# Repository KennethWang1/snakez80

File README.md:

# snakez80

Snake running on a custom Z80 computer. Made for TEJ4MP.

# Requirements

- A Z8400-compatible CPU.
- A TMM2016BP memory chip or compatible.
- A PCB with the KiCAD design (TODO: add link to kicad design), or a breadboard with the equivalent schematic.
- An Arduino Nano.

Connect everything, flash the [loader code](./loader) with the Arduino IDE, and open [`web/index.html`](web/index.html) or https://creative0708.github.io/snakez80/ in a browser.

Have fun.

# Building `rom.hpp` from source

You'll need a set of [z88dk](https://github.com/z88dk/z88dk) binaries **with** SDCC. Follow its [installation instructions](https://github.com/z88dk/z88dk/wiki/installation) to install it.

Run `make` to build the ROM and convert the ROM into Arduino code.

# License

If for some reason you want to use this code, it's licensed under the [MIT License](/LICENSE).

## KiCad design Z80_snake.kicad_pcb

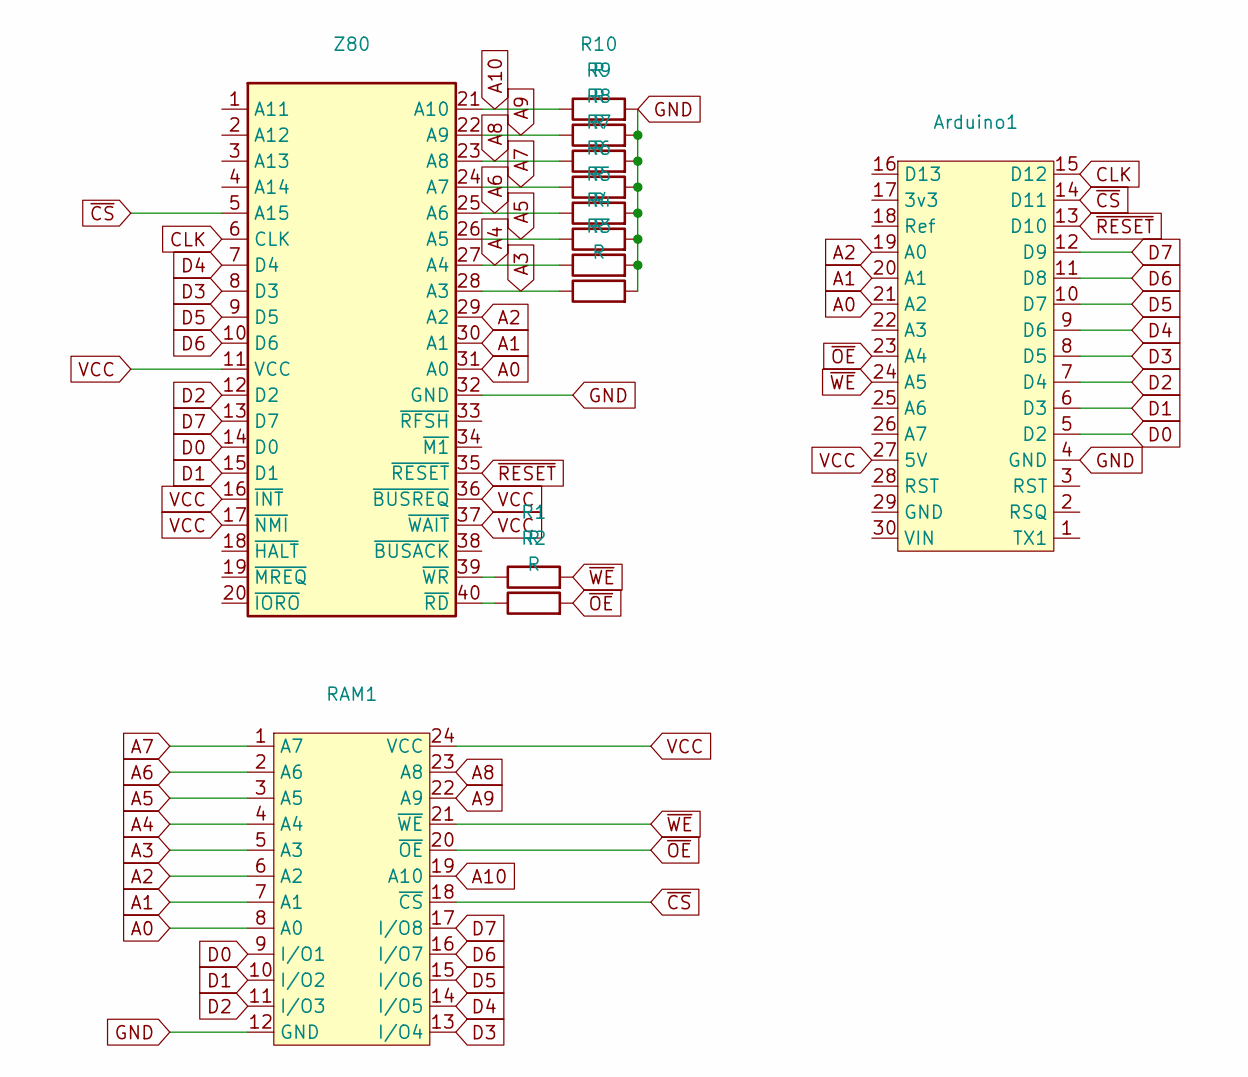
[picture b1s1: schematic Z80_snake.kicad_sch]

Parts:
Arduino1: Arduino_Nano
R1, R2, R3, R4, R5, R6, R7, R8, R9, R10: R; R_Axial_DIN0204_L3.6mm_D1.6mm_P7.62mm_Horizontal
RAM1: RAM
Z80: Z8400AB1

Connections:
A0: Arduino1.21 (A2), RAM1.8 (A0), Z80.31 (A0)
A1: Arduino1.20 (A1), RAM1.7 (A1), Z80.30 (A1)
A2: Arduino1.19 (A0), RAM1.6 (A2), Z80.29 (A2)
A3: R3.1, RAM1.5 (A3), Z80.28 (A3)
A4: R4.1, RAM1.4 (A4), Z80.27 (A4)
A5: R5.1, RAM1.3 (A5), Z80.26 (A5)
A6: R6.1, RAM1.2 (A6), Z80.25 (A6)
A7: R7.1, RAM1.1 (A7), Z80.24 (A7)
A8: R8.1, RAM1.23 (A8), Z80.23 (A8)
A9: R9.1, RAM1.22 (A9), Z80.22 (A9)
A10: R10.1, RAM1.19 (A10), Z80.21 (A10)
CLK: Arduino1.15 (D12), Z80.6 (CLK)
D0: Arduino1.5 (D2), RAM1.9 (I/O1), Z80.14 (D0)
D1: Arduino1.6 (D3), RAM1.10 (I/O2), Z80.15 (D1)
D2: Arduino1.7 (D4), RAM1.11 (I/O3), Z80.12 (D2)
D3: Arduino1.8 (D5), RAM1.13 (I/O4), Z80.8 (D3)
D4: Arduino1.9 (D6), RAM1.14 (I/O5), Z80.7 (D4)
D5: Arduino1.10 (D7), RAM1.15 (I/O6), Z80.9 (D5)
D6: Arduino1.11 (D8), RAM1.16 (I/O7), Z80.10 (D6)
D7: Arduino1.12 (D9), RAM1.17 (I/O8), Z80.13 (D7)
GND: Arduino1.4 (GND), R3.2, R4.2, R5.2, R6.2, R7.2, R8.2, R9.2, R10.2, RAM1.12 (GND), Z80.32 (GND)
unnamed: R2.1, Z80.40 (~RD)
unnamed: R1.1, Z80.39 (~WR)
VCC: Arduino1.27 (5V), RAM1.24 (VCC), Z80.11 (VCC), Z80.16 (~INT), Z80.17 (~NMI), Z80.36 (~BUSREQ), Z80.37 (~WAIT)
~CS: Arduino1.14 (D11), RAM1.18 (~CS), Z80.5 (A15)
~OE: Arduino1.23 (A4), R2.2, RAM1.20 (~OE)
~RESET: Arduino1.13 (D10), Z80.35 (~RESET)
~WE: Arduino1.24 (A5), R1.2, RAM1.21 (~WE)

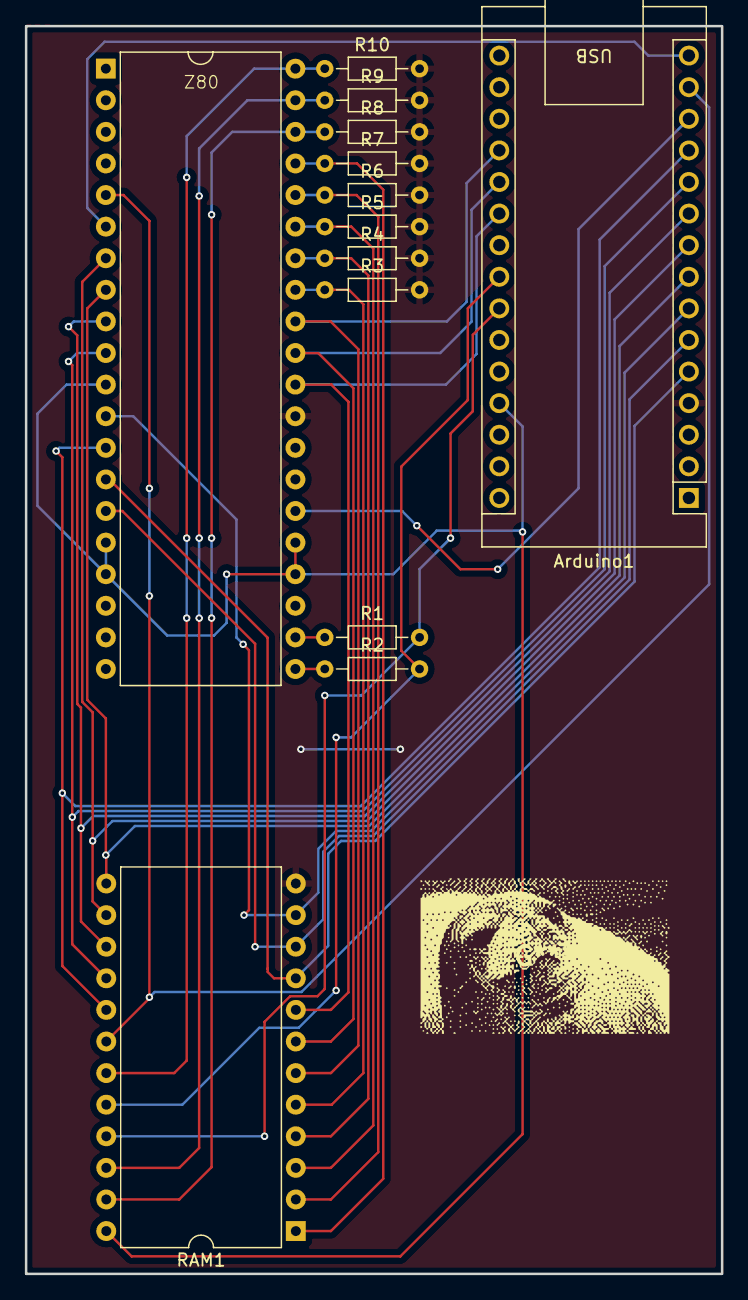
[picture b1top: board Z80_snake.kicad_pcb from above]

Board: 2 copper layers, 55.9 x 100.3 mm, 13 parts (0 on the bottom side), 28 nets.
